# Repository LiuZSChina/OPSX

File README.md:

# OPSX Sonnar
An open sourced Polaroid SX-70 core board with sonnar support.Based on the [OPSX project](https://github.com/sunyitong/OPSX).\
开源的宝丽来sx-70核心板，可以支持带有声呐对焦的设备。基于[OPSX 项目](https://github.com/sunyitong/OPSX)开发。

This is an open sourced Polaroid SX-70 instant camera core board with the Raspberry Pi RP2040 as the MCU. The aim of this project is to provide a fully resource accessible and hobbyist friendly replacement core board. It offers more extensibility and hacking ideas while implementing all the features of the original camera.\
本项目是开源的宝丽来sx-70核心板，该项目使用树莓派rp2040构建而成，本项目的目的是为爱好者提供一个可以完全自主掌控的核心板，在保留原机器各种功能的同时可以发挥自己的创意进行功能拓展。

The structure of the repository:\
本项目仓库的结构：

1. The [Original](https://github.com/LiuZSChina/OPSX/tree/master/Original) file contains design for non-sonnar sx-70.See README.md inside this folder for details.\
[Original](https://github.com/LiuZSChina/OPSX/tree/master/Original)文件夹内是适合没有声呐对焦sx70的核心板设计，设计来自于原本的[OPSX 项目](https://github.com/sunyitong/OPSX)，文件夹内具体项目的作用详见文件夹内的README.md

2. The [Sonar](https://github.com/LiuZSChina/OPSX/tree/master/Sonnar) file contains design for sonnar sx-70.See README.md inside this folder for details.\
[Original](https://github.com/LiuZSChina/OPSX/tree/master/Original)文件夹内是新设计的适用于声呐对焦的sx70核心板及附件，文件夹内具体项目的作用详见文件夹内的README.md。

## Table of Contents

- [OPSX](#opsx)
  - [Hardware](#hardware)
    - [Fabrication](#fabrication)
  - [Software](#software)
    - [Uploading](#uploading)
  - [Contributor](#contributor)
  - [License](#license)

## Hardware
> Remander: You are going to need some “basic” tools:   soldering iron with a fine tip, a prying tool and a tweezer.\
Aside from the usual tools you are going to need what is called a “Polaroid screwdriver” or “SX-70 screwdriver”, since most of the cameras use a special “square 1mm x 1mm” screws. You could either buy one or fabricate one yourself.\
please read the [Disassembly Guide](https://instantphotography.files.wordpress.com/2010/12/polaroid-sx-70-camera-repair-book.pdf) or [SX70 camera 125ASA to 600ASA conversion](https://opensx70.com/tutorials/100-600-conversion/) first.\
提示：首先你需要一些基本的工具：电烙铁、撬棒和镊子。\
其次大多数sx70相机的螺丝都是非常特殊的1mm x 1mm 宝丽来螺丝，所以你需要使用特殊的螺丝刀才能拆卸，买一把或者自己磨一个都可以。\
在操作之前推荐先浏览[Disassembly Guide](https://instantphotography.files.wordpress.com/2010/12/polaroid-sx-70-camera-repair-book.pdf) 或者 [SX70 camera 125ASA to 600ASA conversion](https://opensx70.com/tutorials/100-600-conversion/).

### Fabrication
Please select a **dual copper layer PCB** with a thickness of **0.8 mm** or less for fabrication.\
制造时请选择 FR-4基板，双层板，厚度0.8mm或者更小（会贵）。

## Software
TODO

### Uploading
Solder U+ U- GND VCC to a standard usb cable to connect to your computer. Then you can treat it as normal raspberry pico device. See [here](https://www.raspberrypi.com/documentation/microcontrollers/rp2040.html#raspberry-pi-pico) for more information about uploading.\
把板子上的U+ U- GND VCC焊到usb线上，连接电脑后可以当作树莓派Pico开发板进行操作，具体上传的方法在[这里](https://www.raspberrypi.com/documentation/microcontrollers/rp2040.html#raspberry-pi-pico)。

## Contributor
[@Yitong Sun](https://github.com/sunyitong) - a PhD candidate in the Computer Science Research Centre at the Royal College of Art.[RCA website](https://www.rca.ac.uk/research-innovation/research-degrees/research-students/yitong-sun/) - [E-mail](yitong.sun@network.rca.ac.uk)

[@LiuZS](https://github.com/LiuZSChina) - ？
## License
Any distribution or modification based on this project should be clearly attributed to the source.
[GPL 3.0](LICENSE)

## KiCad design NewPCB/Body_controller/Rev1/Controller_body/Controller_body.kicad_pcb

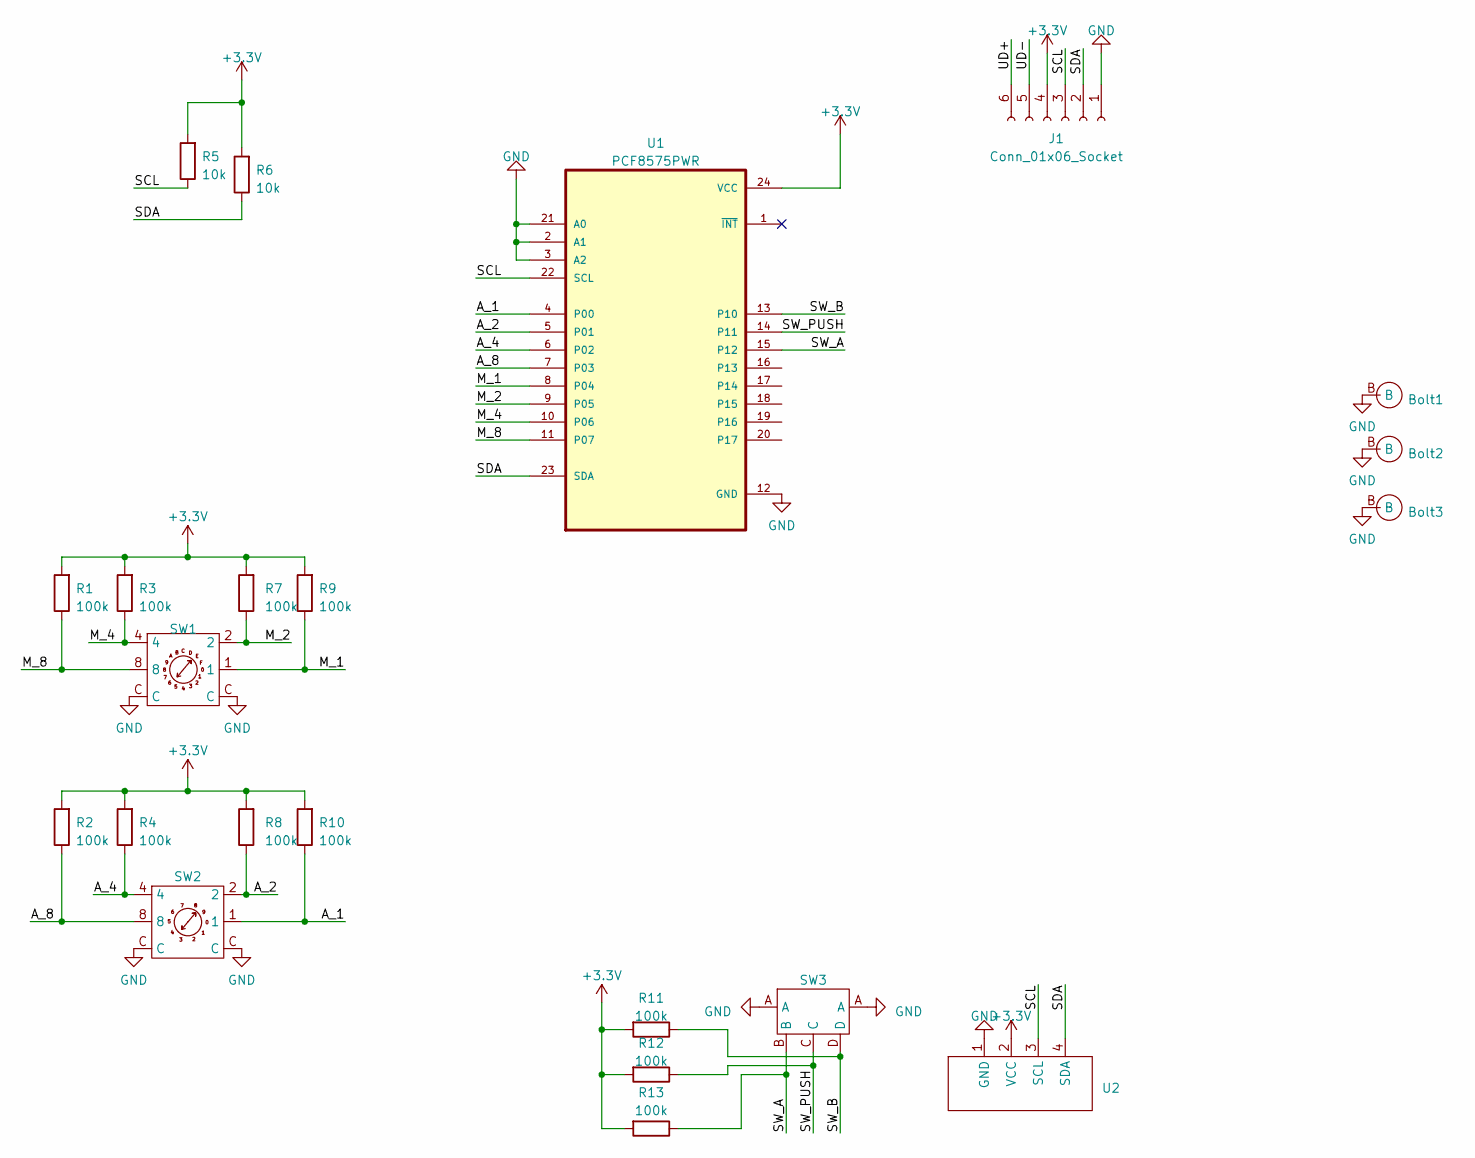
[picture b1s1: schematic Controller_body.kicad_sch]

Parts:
Bolt1, Bolt2, Bolt3: M3_Bolt
J1: Conn_01x06_Socket; TE_84953-6_1x06-1MP_P1.0mm_Horizontal
R1, R2, R3, R4, R7, R8, R9, R10, R11, R12, R13: 100k; R_0805_2012Metric_Pad1.20x1.40mm_HandSolder
R5, R6: 10k; R_0805_2012Metric_Pad1.20x1.40mm_HandSolder
SW1: GSMR_16
SW2: GSMR_10S
SW3: Direction3 Pin5
U1: PCF8575PWR; SOP65P640X120-24N
U2: OLED 0.96 i2c

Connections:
+3.3V: J1.4, R1.2, R2.2, R3.2, R4.2, R5.2, R6.2, R7.2, R8.2, R9.2, R10.2, R11.2, R12.2, R13.2, U1.24 (VCC), U2.2 (VCC)
/A_1: R10.1, SW2.1, U1.4 (P00)
/A_2: R8.1, SW2.2, U1.5 (P01)
/A_4: R4.1, SW2.4, U1.6 (P02)
/A_8: R2.1, SW2.8, U1.7 (P03)
/M_1: R9.1, SW1.1, U1.8 (P04)
/M_2: R7.1, SW1.2, U1.9 (P05)
/M_4: R3.1, SW1.4, U1.10 (P06)
/M_8: R1.1, SW1.8, U1.11 (P07)
/SCL: J1.3, R5.1, U1.22 (SCL), U2.3 (SCL)
/SDA: J1.2, R6.1, U1.23 (SDA), U2.4 (SDA)
/SW_A: R13.1, SW3.B, U1.15 (P12)
/SW_B: R11.1, SW3.D, U1.13 (P10)
/SW_PUSH: R12.1, SW3.C, U1.14 (P11)
/UD+: J1.6
/UD-: J1.5
GND: Bolt1.B, Bolt2.B, Bolt3.B, J1.1, SW1.C, SW2.C, SW3.A, U1.2 (A1), U1.3 (A2), U1.12 (GND), U1.21 (A0), U2.1 (GND)

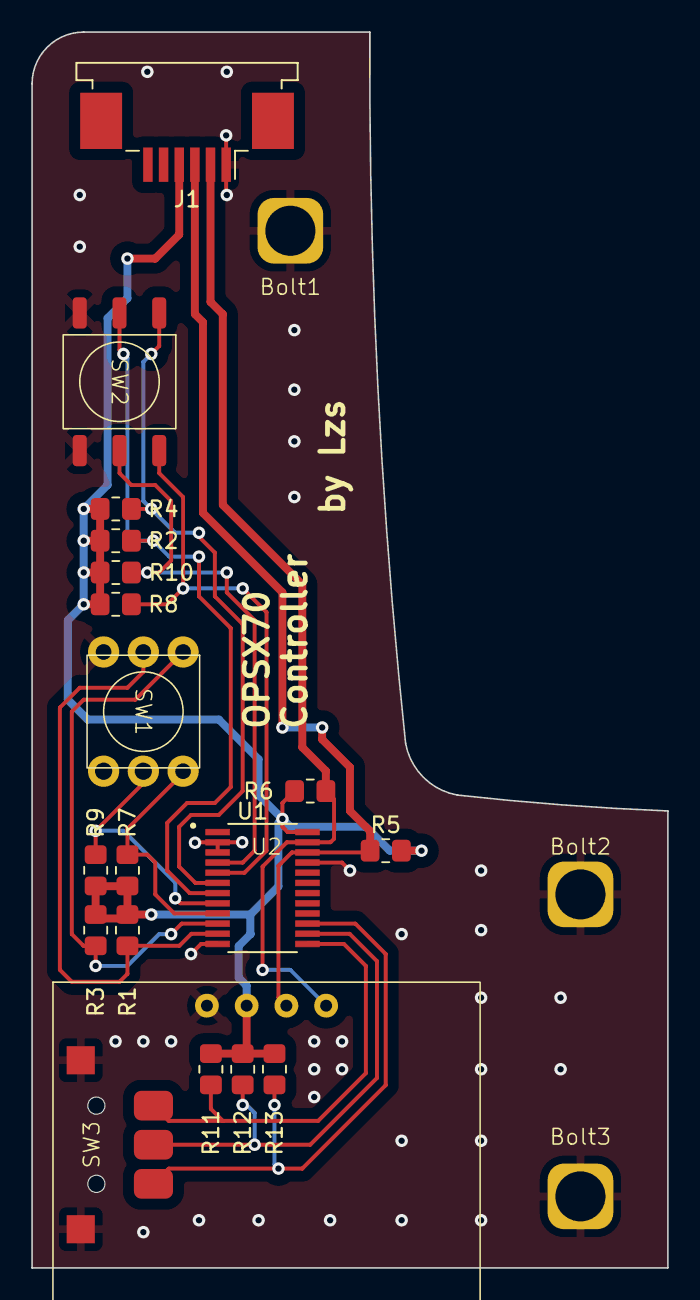
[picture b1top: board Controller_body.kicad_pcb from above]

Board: 2 copper layers, 40.6 x 79.0 mm, 22 parts (0 on the bottom side), 15 nets.

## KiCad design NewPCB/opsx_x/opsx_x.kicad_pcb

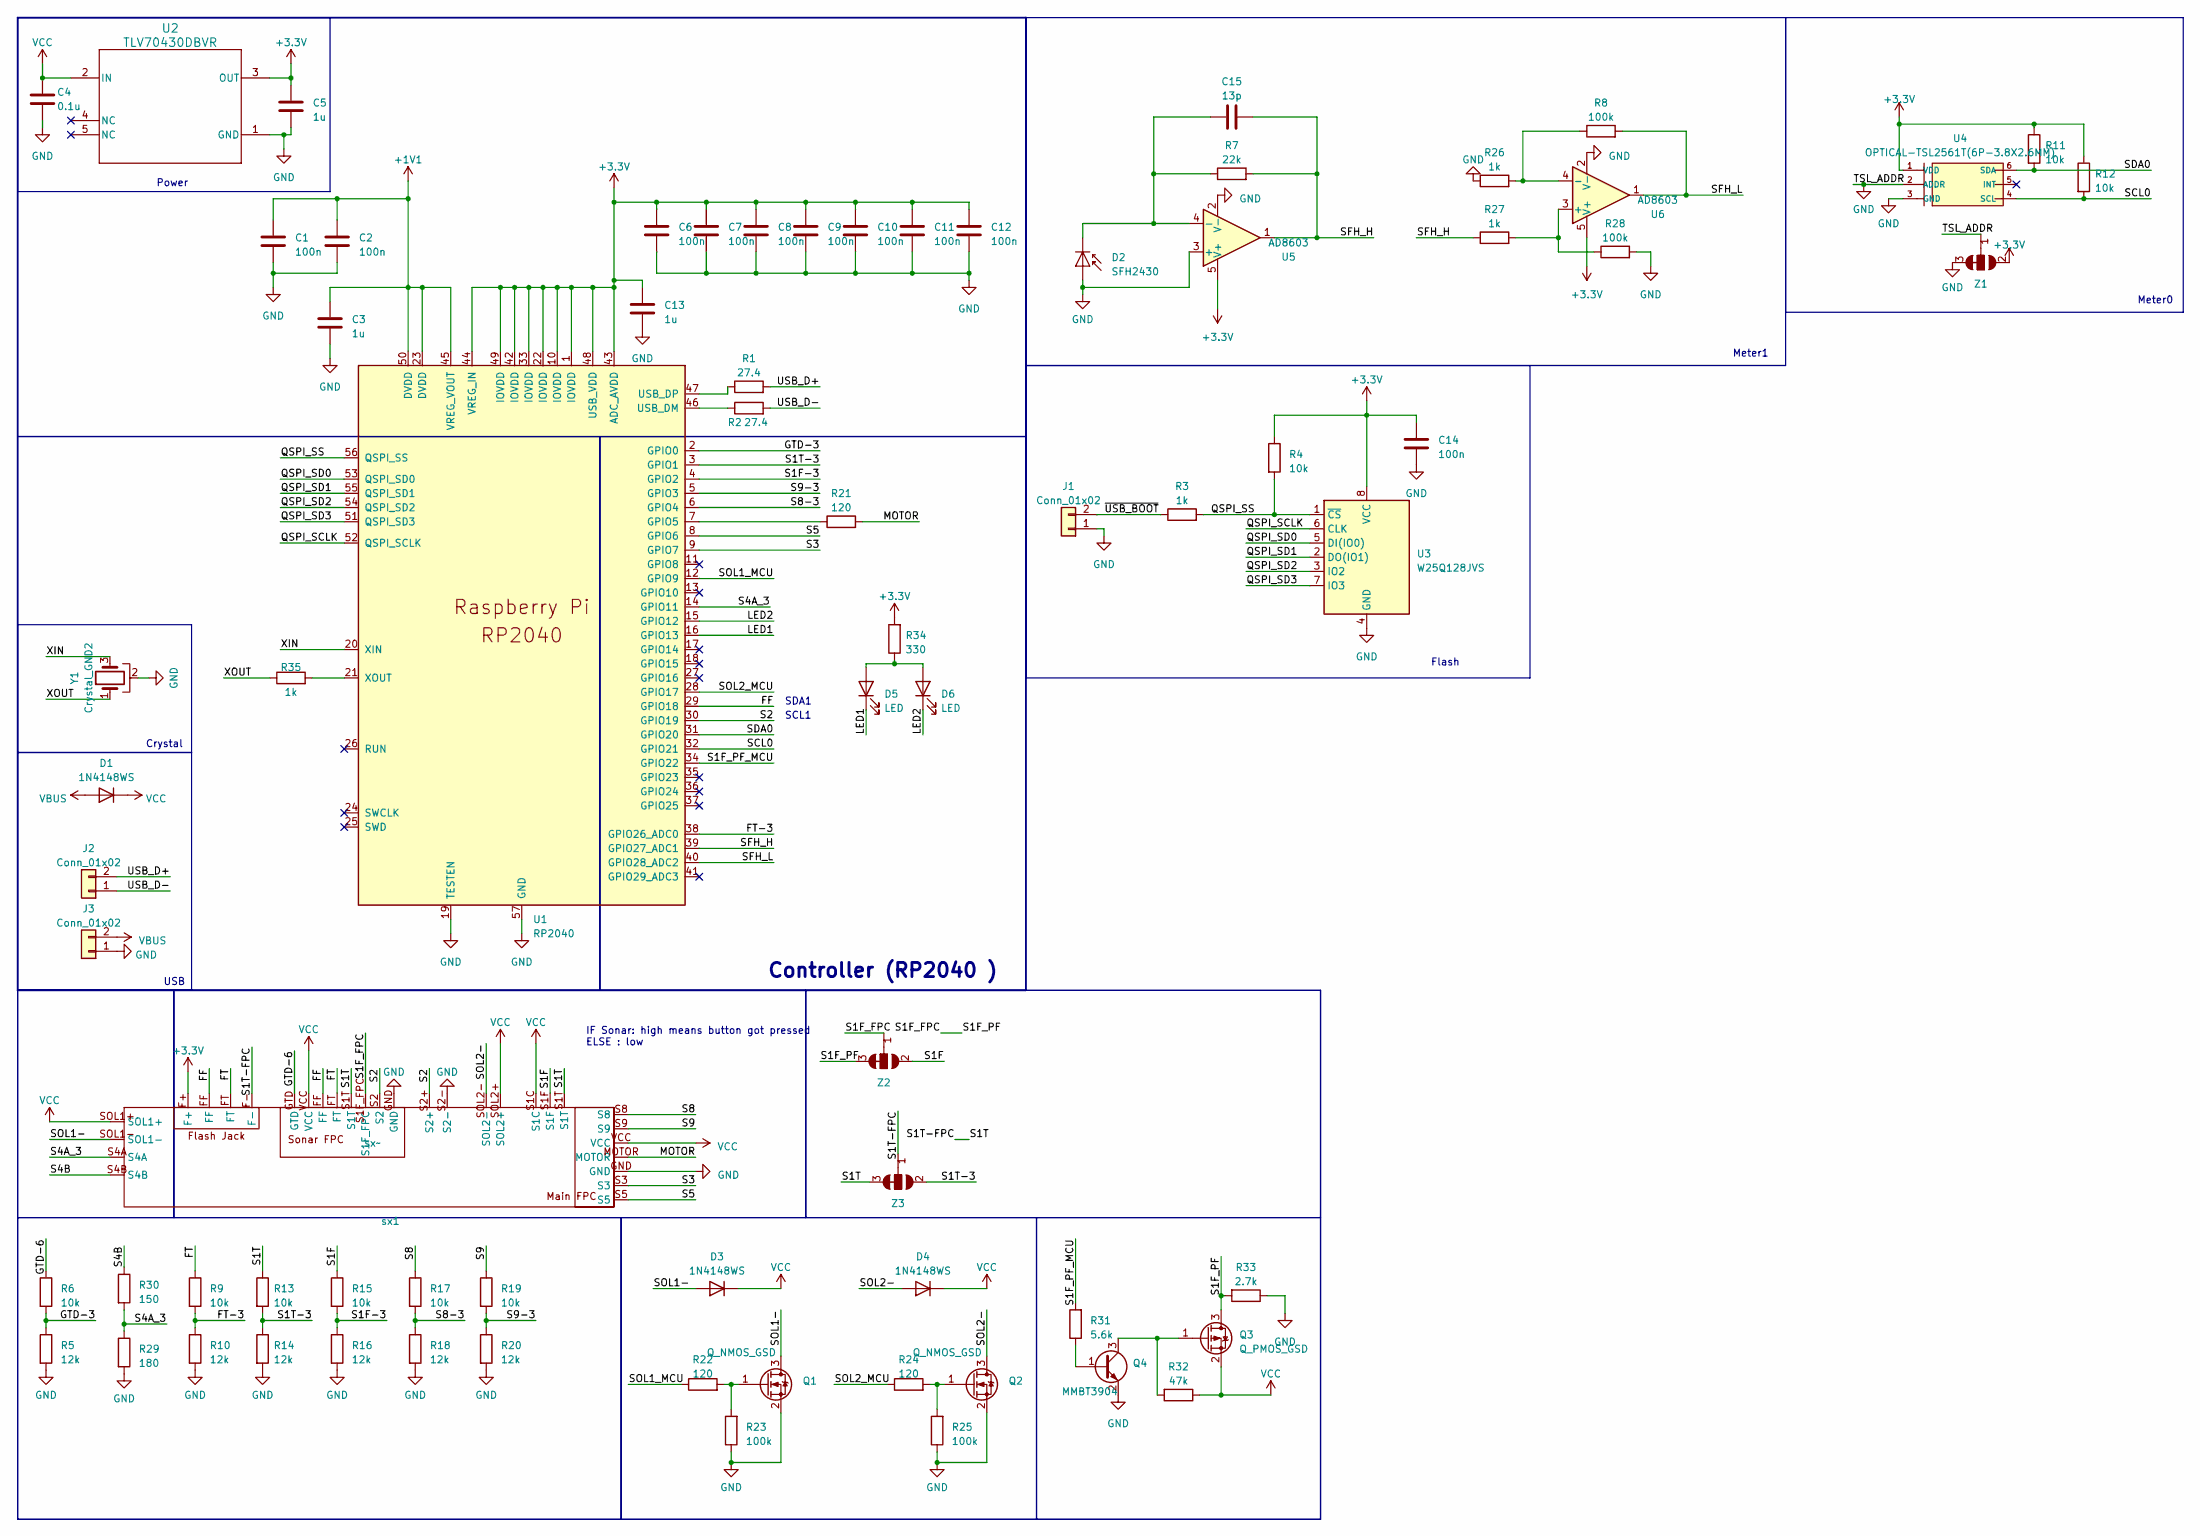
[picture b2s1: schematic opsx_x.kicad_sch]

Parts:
C1, C2, C6, C7, C8, C9, C10, C11, C12, C14: 100n; C_0402_1005Metric_Pad0.74x0.62mm_HandSolder
C3, C5, C13: 1u; C_0402_1005Metric_Pad0.74x0.62mm_HandSolder
C4: 0.1u; C_0402_1005Metric_Pad0.74x0.62mm_HandSolder
C15: 13p; C_0402_1005Metric_Pad0.74x0.62mm_HandSolder
D1, D3, D4: 1N4148WS; D_SOD-323
D2: SFH2430; Osram_SFH2430
D5, D6: LED; D_0603_1608Metric_Pad1.05x0.95mm_HandSolder
J1, J2, J3: Conn_01x02; PinHeader_1x02_P2.54mm_Vertical
Q1, Q2: Q_NMOS_GSD; SOT-23
Q3: Q_PMOS_GSD; SOT-23
Q4: MMBT3904; SOT-23
R1, R2: 27.4; R_0402_1005Metric_Pad0.72x0.64mm_HandSolder
R3, R26, R27, R35: 1k; R_0402_1005Metric_Pad0.72x0.64mm_HandSolder
R4, R6, R9, R11, R12, R13, R15, R17, R19: 10k; R_0402_1005Metric_Pad0.72x0.64mm_HandSolder
R5, R10, R14, R16, R18, R20: 12k; R_0402_1005Metric_Pad0.72x0.64mm_HandSolder
R7: 22k; R_0805_2012Metric_Pad1.20x1.40mm_HandSolder
R8, R23, R25, R28: 100k; R_0402_1005Metric_Pad0.72x0.64mm_HandSolder
R21, R22, R24: 120; R_0402_1005Metric_Pad0.72x0.64mm_HandSolder
R29: 180; R_0402_1005Metric_Pad0.72x0.64mm_HandSolder
R30: 150; R_0402_1005Metric_Pad0.72x0.64mm_HandSolder
R31: 5.6k; R_0402_1005Metric_Pad0.72x0.64mm_HandSolder
R32: 47k; R_0402_1005Metric_Pad0.72x0.64mm_HandSolder
R33: 2.7k; R_0402_1005Metric_Pad0.72x0.64mm_HandSolder
R34: 330; R_0402_1005Metric_Pad0.72x0.64mm_HandSolder
U1: RP2040; RP2040-QFN-56
U2: TLV70430DBVR; DBV0005A_N
U3: W25Q128JVS; SOIC-8_5.23x5.23mm_P1.27mm
U4: OPTICAL-TSL2561T(6P-3.8X2.6MM); TMB6-1.55-3.8X2.6MM; MPN TSL2561T
U5, U6: AD8603; TSOT-23-5
Y1: Crystal_GND2; Resonator_SMD_Murata_CSTxExxV-3Pin_3.0x1.1mm
Z1, Z2, Z3: Selector_default
sx1: sx~; sx70

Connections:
+1V1: C1.1, C2.1, C3.1, U1.23 (DVDD), U1.45 (VREG_VOUT), U1.50 (DVDD)
+3.3V: C5.1, C6.1, C7.1, C8.1, C9.1, C10.1, C11.1, C12.1, C13.1, C14.1, R4.1, R11.1, R12.1, R34.2, U1.1 (IOVDD), U1.10 (IOVDD), U1.22 (IOVDD), U1.33 (IOVDD), U1.42 (IOVDD), U1.43 (ADC_AVDD), U1.44 (VREG_IN), U1.48 (USB_VDD), U1.49 (IOVDD), U2.3 (OUT), U3.8 (VCC), U4.1 (VDD), U5.5 (V+), U6.5 (V+), Z1.1, sx1.F+
/FF: U1.29 (GPIO18), sx1.FF
/FT: R9.1, sx1.FT
/FT-3: R9.2, R10.1, U1.38 (GPIO26_ADC0)
/GTD-3: R5.1, R6.2, U1.2 (GPIO0)
/GTD-6: R6.1, sx1.GTD
/LED1: D5.1 (K), U1.16 (GPIO13)
/LED2: D6.1 (K), U1.15 (GPIO12)
/MOTOR: R21.2, sx1.MOTOR
/QSPI_SCLK: U1.52 (QSPI_SCLK), U3.6 (CLK)
/QSPI_SD0: U1.53 (QSPI_SD0), U3.5 (DI(IO0))
/QSPI_SD1: U1.55 (QSPI_SD1), U3.2 (DO(IO1))
/QSPI_SD2: U1.54 (QSPI_SD2), U3.3 (IO2)
/QSPI_SD3: U1.51 (QSPI_SD3), U3.7 (IO3)
/QSPI_SS: R3.2, R4.2, U1.56 (QSPI_SS), U3.1 (~CS)
/S1F: R15.1, Z2.1, sx1.S1F
/S1F-3: R15.2, R16.1, U1.4 (GPIO2)
/S1F_FPC: Q3.3 (D), R33.2, Z2.2, Z2.3, sx1.S1F_FPC
/S1F_PF_MCU: R31.2, U1.34 (GPIO22)
/S1T: R13.1, Z3.2, Z3.3, sx1.F-, sx1.S1T
/S1T-3: R13.2, R14.1, U1.3 (GPIO1), Z3.1
/S2: U1.30 (GPIO19), sx1.S2, sx1.S2+
/S3: U1.9 (GPIO7), sx1.S3
/S4A_3: R29.1, R30.2, U1.14 (GPIO11), sx1.S4A
/S4B: R30.1, sx1.S4B
/S5: U1.8 (GPIO6), sx1.S5
/S8: R17.1, sx1.S8
/S8-3: R17.2, R18.1, U1.6 (GPIO4)
/S9: R19.1, sx1.S9
/S9-3: R19.2, R20.1, U1.5 (GPIO3)
/SCL0: R12.2, U1.32 (GPIO21), U4.4 (SCL)
/SDA0: R11.2, U1.31 (GPIO20), U4.6 (SDA)
/SFH_H: C15.2, R7.2, R27.1, U1.39 (GPIO27_ADC1), U5.1
/SFH_L: R8.2, U1.40 (GPIO28_ADC2), U6.1
/SOL1-: D3.2 (A), Q1.3 (D), sx1.SOL1-
/SOL1_MCU: R22.1, U1.12 (GPIO9)
/SOL2-: D4.2 (A), Q2.3 (D), sx1.SOL2-
/SOL2_MCU: R24.1, U1.28 (GPIO17)
/USB_D+: J2.2, R1.2
/USB_D-: J2.1, R2.2
/XIN: U1.20 (XIN), Y1.3
/XOUT: R35.1, Y1.1
/~USB_BOOT: J1.2, R3.1
GND: C1.2, C2.2, C3.2, C4.2, C5.2, C6.2, C7.2, C8.2, C9.2, C10.2, C11.2, C12.2, C13.2, C14.2, D2.2 (A), J1.1, J3.1, Q1.2 (S), Q2.2 (S), Q4.2 (E), R5.2, R10.2, R14.2, R16.2, R18.2, R20.2, R23.1, R25.1, R26.1, R28.2, R29.2, R33.1, U1.19 (TESTEN), U1.57 (GND), U2.1 (GND), U3.4 (GND), U4.2 (ADDR), U4.3 (GND), U5.2 (V-), U5.3 (+), U6.2 (V-), Y1.2, Z1.2, Z1.3, sx1.GND, sx1.S2-
unnamed: C15.1, D2.1 (K), R7.1, U5.4 (-)
unnamed: D5.2 (A), D6.2 (A), R34.1
unnamed: Q1.1 (G), R22.2, R23.2
unnamed: Q2.1 (G), R24.2, R25.2
unnamed: Q3.1 (G), Q4.3 (C), R32.2
unnamed: Q4.1 (B), R31.1
unnamed: R21.1, U1.7 (GPIO5)
unnamed: R2.1, U1.46 (USB_DM)
unnamed: R1.1, U1.47 (USB_DP)
unnamed: R35.2, U1.21 (XOUT)
unnamed: R27.2, R28.1, U6.3 (+)
unnamed: R8.1, R26.2, U6.4 (-)
VBUS: D1.2 (A), J3.2
VCC: C4.1, D1.1 (K), D3.1 (K), D4.1 (K), Q3.2 (S), R32.1, U2.2 (IN), sx1.S1C, sx1.SOL1+, sx1.SOL2+, sx1.VCC

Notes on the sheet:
Flash
Meter0
Power
Crystal
IF Sonar: high means button got pressed ELSE : low
Controller (RP2040 )
Meter1
SCL1
SDA1
USB

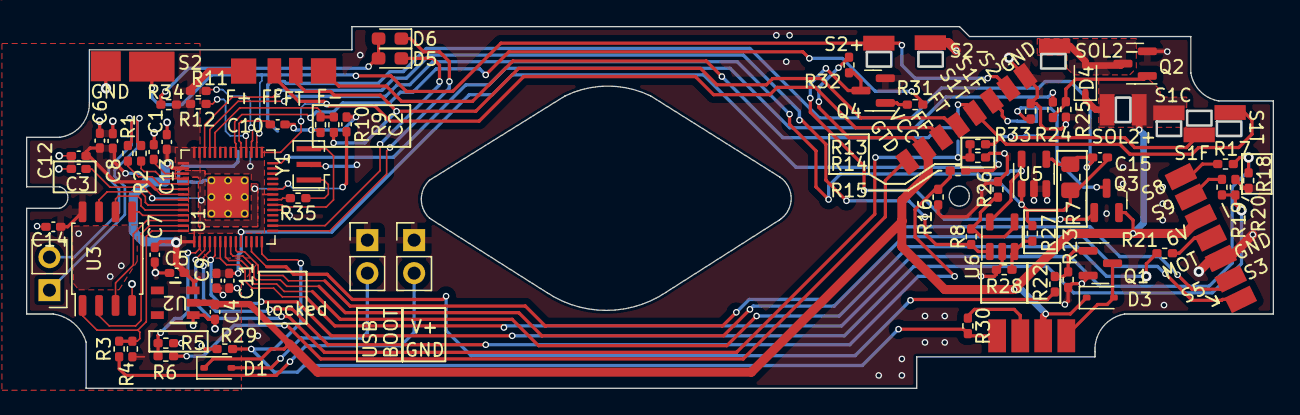
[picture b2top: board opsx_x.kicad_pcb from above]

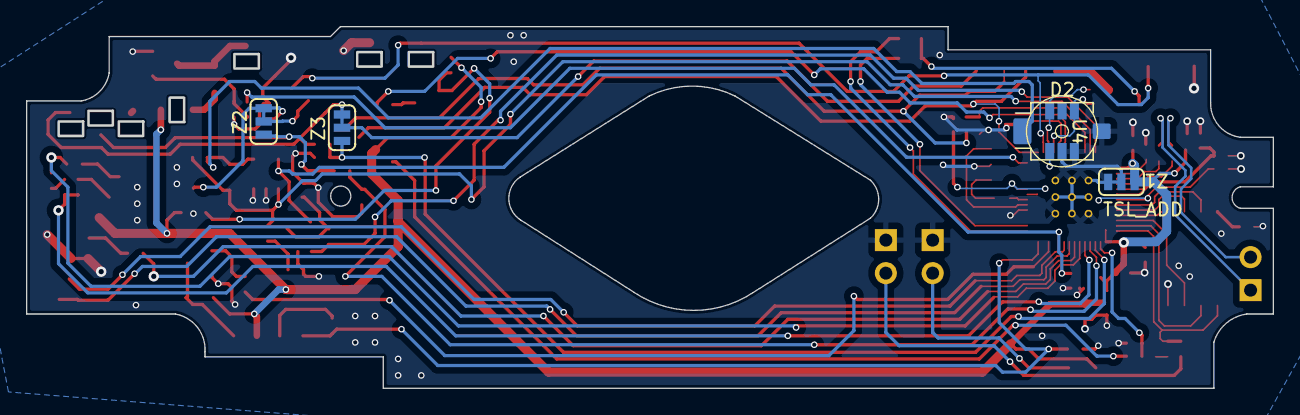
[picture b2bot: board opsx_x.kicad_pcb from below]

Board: 2 copper layers, 95.8 x 27.7 mm, 74 parts (5 on the bottom side), 59 nets.

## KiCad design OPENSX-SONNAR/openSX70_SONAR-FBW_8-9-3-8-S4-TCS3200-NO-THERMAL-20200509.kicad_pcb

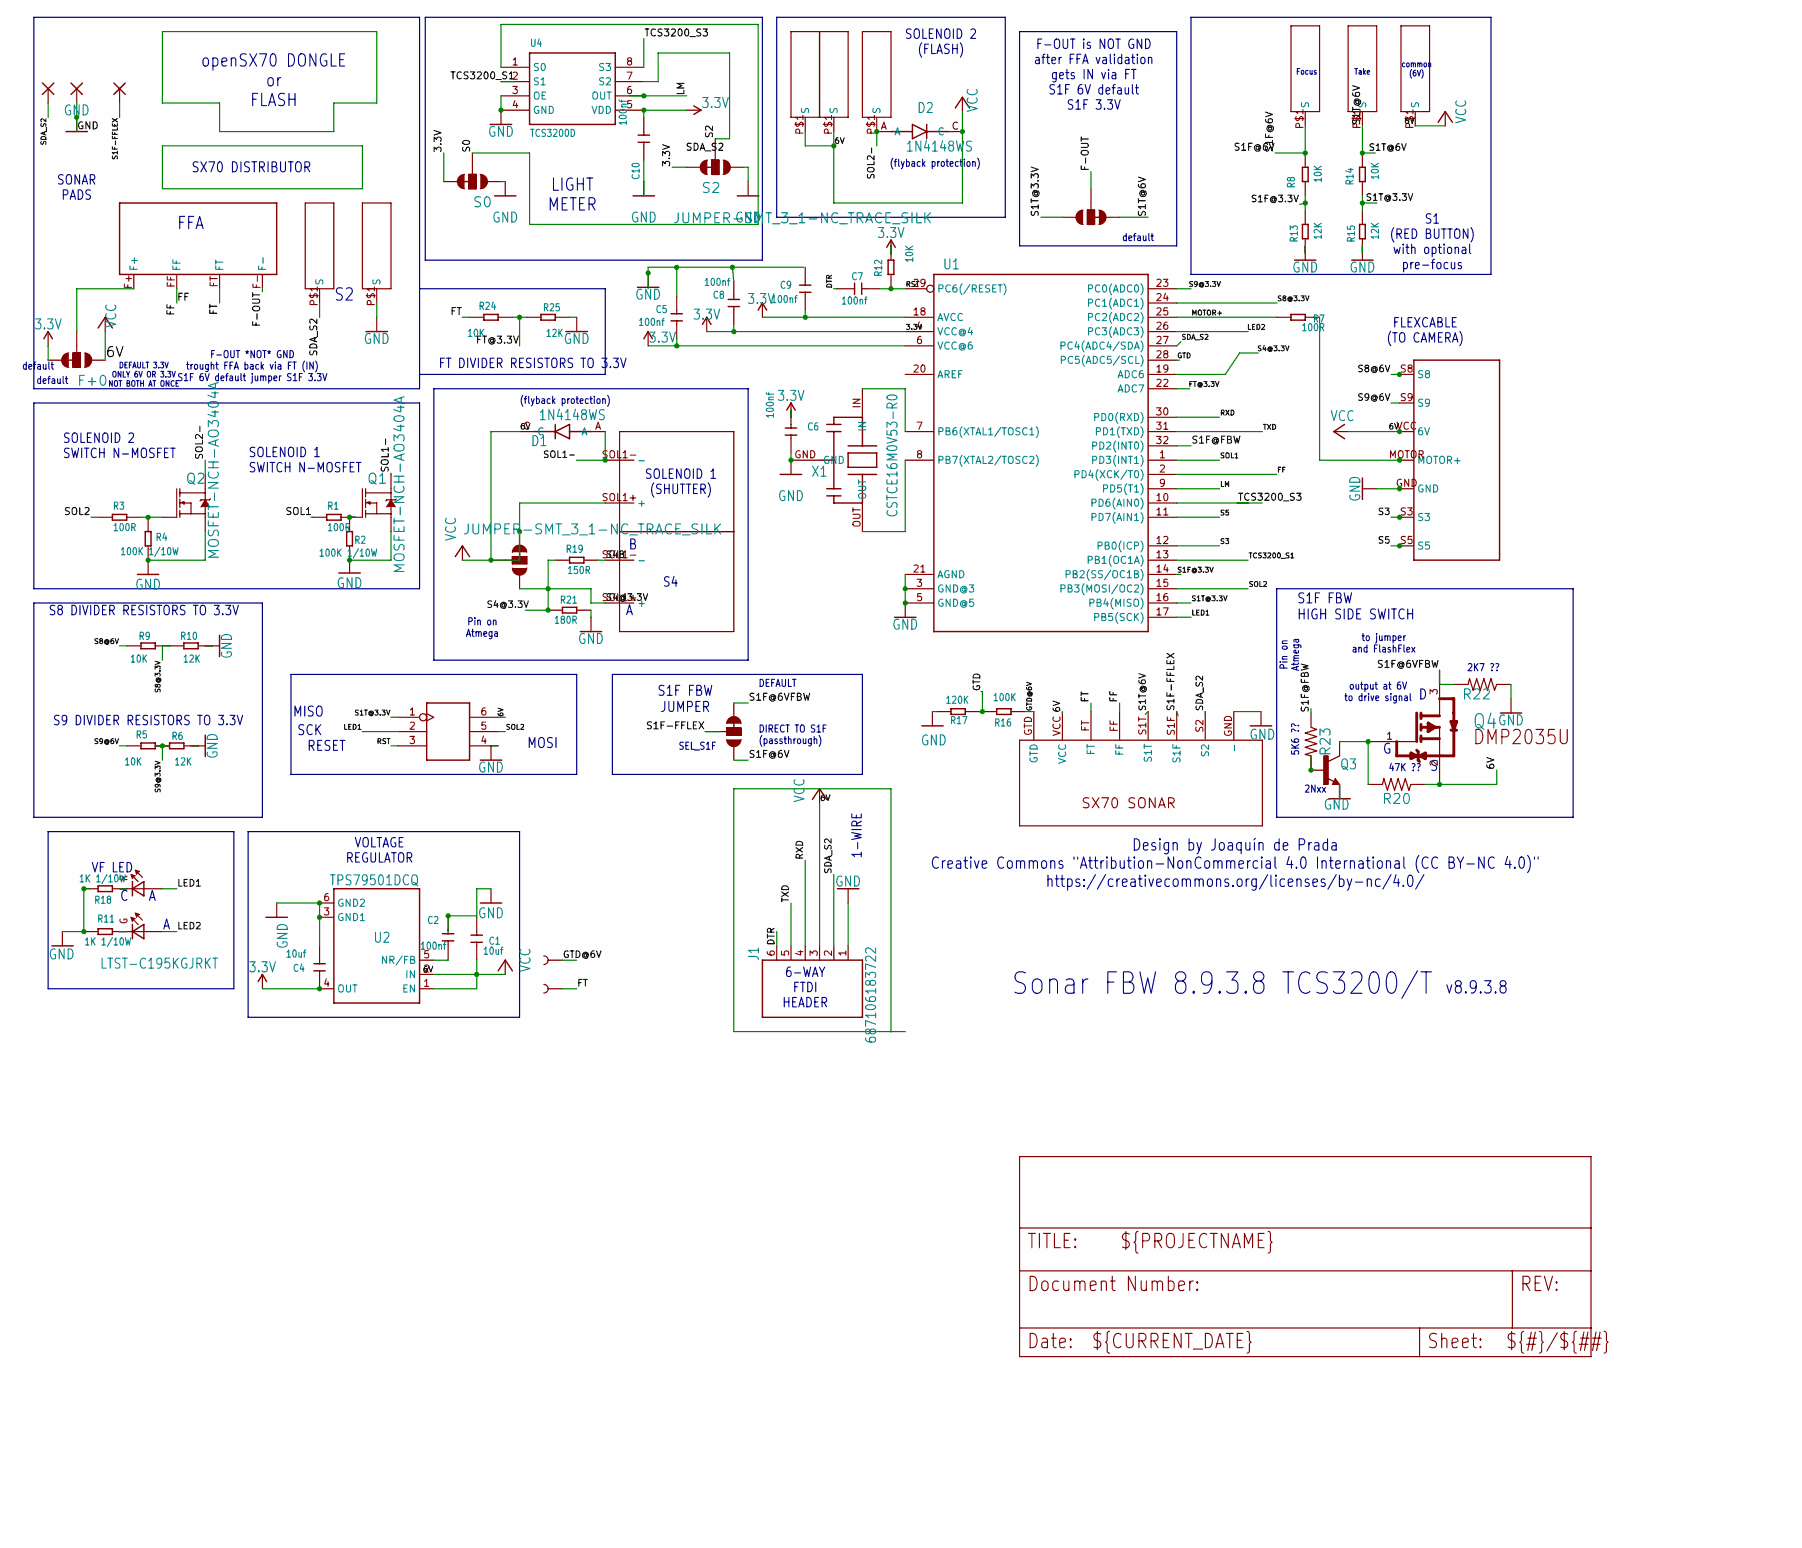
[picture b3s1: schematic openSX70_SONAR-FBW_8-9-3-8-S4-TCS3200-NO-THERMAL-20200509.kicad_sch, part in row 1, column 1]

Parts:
C1, C4: 10uf; C0603
C2, C5, C6, C7, C8, C9, C10: 100nf; C0603
D1, D2: 1N4148WS; SODFL2512X100N
F+0: JUMPER-SMT_3_1-NC_TRACE_SILK; SMT-JUMPER_3_1-NC_TRACE_SILK
ICSP0: ICSP; H2X3-2.54
J1: 687106183722
LED0: LTST-C195KGJRKT; LTST-BILED-15X16
Q1, Q2: MOSFET-NCH-AO3404A; SOT23-3
Q3: -NPN-SOT23-BEC; SOT23-BEC
Q4: DIODES_INC._DMP2035UDIODES_INC._DMP2035U_0_2; DIODES_INC._DMP2035U_2
R1, R3, R7: 100R; R0603
R2, R4: 100K 1/10W; R0603
R5, R8, R9, R12, R14, R24: 10K; R0603
R6, R10, R13, R15, R25: 12K; R0603
R11, R18: 1K 1/10W; R0603
R16: 100K; R0603
R17: 120K; R0603
R19: 150R; R0603
R20, R22, R23: RESISTOR0603; 0603
R21: 180R; R0603
S0, S2: JUMPER-SMT_3_1-NC_TRACE_SILK; SMT-JUMPER_3_1-NC_TRACE_SILK
S1-0, S1F+0, S1T+0, S2+0, S2-0: SX70-S-PAD-NEW; SX70-S-PAD2
S4: SX70-SOLENOID1-2PADS; SX70-SOLENOID1-2
SEL_F-0: JUMPER-SMT_3_1-NC_TRACE_SILK; SMT-JUMPER_3_1-NC_TRACE_SILK
SEL_S1F0, SEL_S4: JUMPER-SMT_3_1-NC_TRACE_SILK; SMT-JUMPER_3_1-NC_TRACE_SILK
SOL1: SX70-SOLENOID1-2PADS; SX70-SOLENOID1-2
SOL2+0, SOL2+1, SOL2-0: SX70-S-PAD-NEW; SX70-S-PAD2
TP1, TP4: TEST-POINT3X4; PAD.03X.04
U1: ATMEGA328P_32MLFATMEGA328-MLF; MLF32
U2: TPS79501DCQ; SOT127P706X180-6N
U4: TCS3200D; SOIC8
U$1: SX70-7-PAD; SX70-7-PAD-PROPER
U$2: FFA; FFA-PAD-PACKAGE
U$3: SX70-SONAR-FLASHFLEX; SONAR-FLASHFLEX
U$5, U$6: S2-SONAR
U$7: GND-SONAR
X1: CSTCE16M0V53-R0; CFP95P160X100-3N

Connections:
3.3V: C4.2, C5.1, C6.1, C8.1, C9.1, C10.1, F+0.3, R12.2, S0.3, S2.3, U1.4 (VCC@4), U1.6 (VCC@6), U1.18 (AVCC), U2.4 (OUT), U4.5 (VDD)
6V: C1.2, D1.C, D2.C, F+0.1, ICSP0.6 (VCC), J1.3 (4), Q4.2 (S), R20.1, S1-0.P$1, SEL_S4.2, SEL_S4.3, SOL1.SOL1+ (+), SOL2+0.P$1, SOL2+1.P$1, U2.1 (EN), U2.2 (IN), U$1.VCC (6V), U$3.VCC
DTR: C7.1, J1.6 (1)
F-OUT: SEL_F-0.2, U$2.F-
FF: U1.2 (PD4(XCK/T0)), U$2.FF, U$3.FF
FT: R24.1, TP4.P$1, U$2.FT, U$3.FT
FT@3.3V: R24.2, R25.1, U1.22 (ADC7)
GND: C1.1, C2.1, C4.1, C5.2, C6.2, C8.2, C10.2, ICSP0.4 (GND), J1.1 (6), Q1.2 (S), Q2.2 (S), Q3.E, R2.1, R4.1, R6.2, R10.2, R11.1, R13.1, R15.1, R17.1, R18.2, R21.1, R22.1, R25.2, S0.1, S2.1, S2-0.P$1, U1.3 (GND@3), U1.5 (GND@5), U1.21 (AGND), U2.3 (GND1), U2.6 (GND2), U4.3 (OE), U4.4 (GND), U$1.GND, U$3.GND (-), U$7.GND-SONAR, X1.GND
GTD: R16.2, R17.2, U1.28 (PC5(ADC5/SCL))
GTD@6V: R16.1, TP1.P$1, U$3.GTD
LED1: ICSP0.2 (SCK), LED0.P$2 (A2), U1.17 (PB5(SCK))
LED2: LED0.P$1 (A1), U1.26 (PC3(ADC3))
LM: U1.9 (PD5(T1)), U4.6 (OUT)
MOTOR+: R7.1, U1.25 (PC2(ADC2))
MOTOR-HEADER: R7.2, U$1.MOTOR (MOTOR+)
unnamed: Q1.1 (G), R1.2, R2.2
unnamed: LED0.P$4 (K2), R18.1
unnamed: Q2.1 (G), R3.2, R4.2
unnamed: U1.7 (PB6(XTAL1/TOSC1)), X1.IN
unnamed: F+0.2, U$2.F+
unnamed: U1.8 (PB7(XTAL2/TOSC2)), X1.OUT
unnamed: Q3.C, Q4.1 (G), R20.2
unnamed: Q3.B, R23.2
unnamed: C2.2, U2.5 (NR/FB)
unnamed: LED0.P$3 (K1), R11.2
RST: C7.2, ICSP0.3 (RST), R12.1, U1.29 (PC6(/RESET))
RXD: J1.4 (3), U1.30 (PD0(RXD))
S0: S0.2, U4.1 (S0)
S1F-FFLEX: SEL_S1F0.2, U$3.S1F, U$6.S2-SONAR
S1F@3.3V: R8.1, R13.2, U1.14 (PB2(SS/OC1B))
S1F@6V: R8.2, S1F+0.P$1, SEL_S1F0.1
S1F@6VFBW: Q4.3 (D), R22.2, SEL_S1F0.3
S1F@FBW: R23.1, U1.32 (PD2(INT0))
S1T@3.3V: ICSP0.1 (MISO), R14.1, R15.2, SEL_F-0.1, U1.16 (PB4(MISO))
S1T@6V: R14.2, S1T+0.P$1, SEL_F-0.3, U$3.S1T
S2: S2.2, U4.7 (S2)
S3: U1.12 (PB0(ICP)), U$1.S3
S4@3.3V: R19.1, R21.2, S4.SOL1+ (+), SEL_S4.1, U1.19 (ADC6)
S4B: R19.2, S4.SOL1- (-)
S5: U1.11 (PD7(AIN1)), U$1.S5
S8@3.3V: R9.2, R10.1, U1.24 (PC1(ADC1))
S8@6V: R9.1, U$1.S8
S9@3.3V: R5.2, R6.1, U1.23 (PC0(ADC0))
S9@6V: R5.1, U$1.S9
SDA_S2: J1.2 (5), S2+0.P$1, U1.27 (PC4(ADC4/SDA)), U$3.S2, U$5.S2-SONAR
SOL1: R1.1, U1.1 (PD3(INT1))
SOL1-: D1.A, Q1.3 (D), SOL1.SOL1- (-)
SOL2: ICSP0.5 (MOSI), R3.1, U1.15 (PB3(MOSI/OC2))
SOL2-: D2.A, Q2.3 (D), SOL2-0.P$1
TCS3200_S1: U1.13 (PB1(OC1A)), U4.2 (S1)
TCS3200_S3: U1.10 (PD6(AIN0)), U4.8 (S3)
TXD: J1.5 (2), U1.31 (PD1(TXD))

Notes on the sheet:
FLEXCABLE (TO CAMERA)
(flyback protection)
S1 (RED BUTTON) with optional pre-focus
SOLENOID 1 SWITCH N-MOSFET
default
v8.9.3.8
SCK
DEFAULT
Pin on Atmega
1-WIRE
openSX70 DONGLE or FLASH
output at 6V to drive signal
S9 DIVIDER RESISTORS TO 3.3V
VF LED
FT DIVIDER RESISTORS TO 3.3V
S8 DIVIDER RESISTORS TO 3.3V
2Nxx
47K ??
SOLENOID 1 (SHUTTER)
F-OUT is NOT GND after FFA validation gets IN via FT S1F 6V default S1F 3.3V
F-OUT *NOT* GND trought FFA back via FT (IN) S1F 6V default jumper S1F 3.3V
Focus
5K6 ??
LIGHT METER
Take
DIRECT TO S1F (passthrough)
MISO
SEL_S1F
SX70 DISTRIBUTOR
SOLENOID 2 SWITCH N-MOSFET
RESET
S1F FBW JUMPER
6-WAY FTDI HEADER
common (6V)
MOSI
VOLTAGE REGULATOR
2K7 ??
SONAR PADS
Sonar FBW 8.9.3.8 TCS3200/T
Design by Joaquín de Prada Creative Commons "Attribution-NonCommercial 4.0 International (CC BY-NC 4.0)" https://creativecommons.org/licenses/by-nc/4.0/

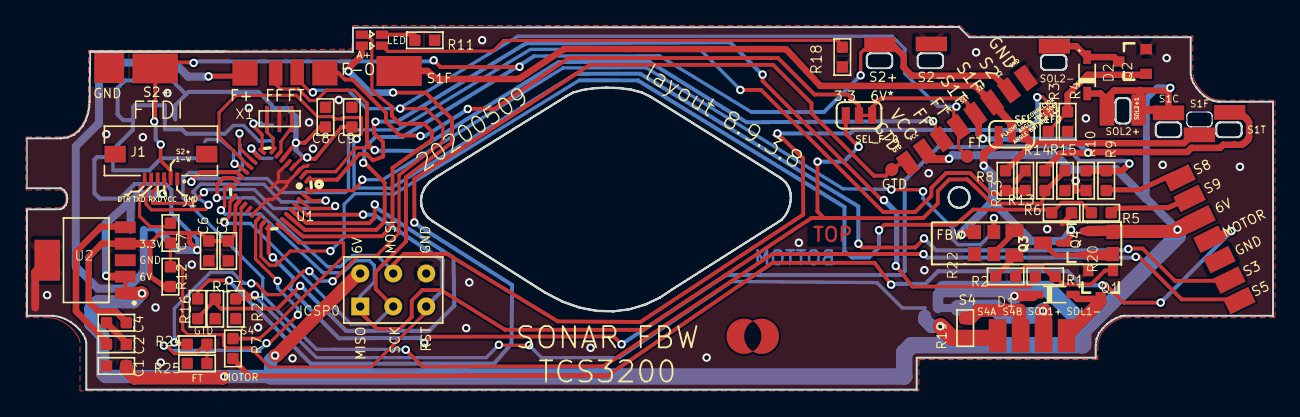
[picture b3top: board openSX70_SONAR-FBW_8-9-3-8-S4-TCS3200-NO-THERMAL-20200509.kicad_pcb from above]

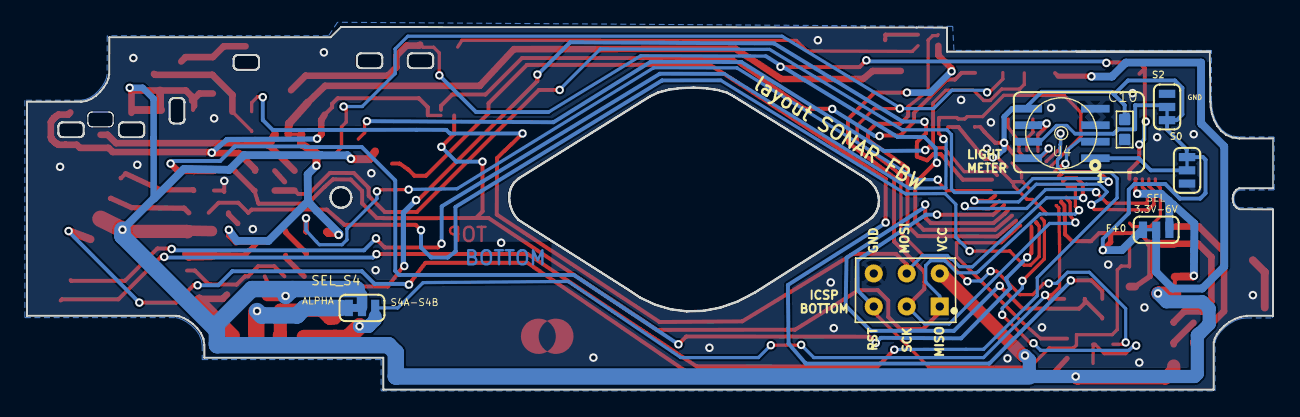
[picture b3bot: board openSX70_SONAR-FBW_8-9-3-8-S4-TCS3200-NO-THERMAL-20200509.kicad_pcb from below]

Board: 2 copper layers, 95.8 x 27.9 mm, 72 parts (6 on the bottom side), 52 nets.

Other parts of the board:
U$8: SONAR-LOGO

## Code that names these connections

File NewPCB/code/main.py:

from machine import Pin,PWM,ADC
import time

_CAMERA_DBG_ = True
Red_Button_Pressed = 1
if_focused = False
de_bounce_time = 1
de_bounce_count = 10
adc_de_bonuce_count = 70
# Code Start at "#End of Config"

# Config Output Pins <See Pins.xls>
shutter_pin = 9
apture_pin = 17
motor_pin = 5
LED_Y_PIN = 12
LED_B_PIN = 13
S1F_FBW_PIN = 22
# End Config Output

# Config Input Pins <See Pins.xls>
S1F_PIN = 2 # Sw 1 Focus
S1T_PIN = 1 # Sw 1 Take Photo
S3_PIN = 7
S5_PIN = 6
ADC_STAGE1_PIN = 27
ADC_STAGE2_PIN = 28
# End Config Input Pins

# Config ShutterDelay  sht(1/n) or sht(n)s
sht4s = 4000
sht3s = 3000
sht2s = 2000
sht1s = 1000
sht2 = 600
#ev75 = 440
sht4 = 280
sht6 =210
sht8 = 155
sht10 =120
sht15 = 97
sht20 = 70
sht30 = 48
#ev115 = 40
sht60 = 33
#ev125 = 29
sht125 = 25
#ev135 = 23
sht250 = 21
#ev145 = 20
sht500 = 19
sht1000 = 18
# End Config ShutterDelay

#End of Config

# Inital camera
def camera_init():
    global motor,shutter,apture,LED_Y,LED_B,s3,s5,s1t,s1f,S1F_FBW,ADC0,ADC1,iso
    shutter = PWM(Pin(shutter_pin))
    shutter.freq(20000)
    shutter.duty_u16(0)
    apture = PWM(Pin(apture_pin))
    apture.freq(70000)
    apture.duty_u16(0)
    
    motor = Pin(motor_pin,Pin.OUT, value=0)
    LED_Y = Pin(LED_Y_PIN, Pin.OUT,value = 1)
    LED_B = Pin(LED_B_PIN, Pin.OUT,value = 1)
    S1F_FBW = Pin(S1F_FBW_PIN, Pin.OUT,value = 0)
    
    s3 = Pin(S3_PIN,Pin.IN,Pin.PULL_UP)
    s5 = Pin(S5_PIN,Pin.IN,Pin.PULL_UP)
    s1f = Pin(S1F_PIN,Pin.IN)
    s1t = Pin(S1T_PIN,Pin.IN)
    
    ADC0 = ADC(Pin(ADC_STAGE1_PIN))  # 初始化ADC
    ADC1 = ADC(Pin(ADC_STAGE2_PIN))  # 初始化ADC
    
    f = open('./dat/iso.txt')
    iso = f.readline()
    iso.replace(" ","")
    f.close()
    if _CAMERA_DBG_:
        print("ISO at %s!"%iso)
    if iso == '600':
        LED_Y.value(0)
    else:
        LED_B.value(0)

def close_led():
    LED_Y.value(1)
    LED_B.value(1)
    
def led_iso():
    if iso == '600':
        LED_Y.value(0)
    else:
        LED_B.value(0)

def de_bounce_read_pins(pin_list):
    global de_bounce_time,de_bounce_count
    pin_value = [0]*len(pin_list)
    for i in range(de_bounce_count):
        for j in range(len(pin_list)):
            pin_value[j] += pin_list[j].value()
        time.sleep_ms(de_bounce_time)
    for i in range(len(pin_value)):
        pin_value[i] = round(pin_value[i]/de_bounce_count)
        if i >1:
            i = 1
    return pin_value

def apture_engage():
    apture.duty_u16(32700)
    
def apture_disengage():
    apture.duty_u16(0)

def meter():
    read_voltage0 = 0
    read_voltage1 = 0
    for i in range(adc_de_bonuce_count):
        read_voltage0 += ADC0.read_u16()*3000/65535   # 读取ADC通道0的数值并根据ADC电压计算公式得到GPIO26引脚上的电压
        read_voltage1 += ADC1.read_u16()*3000/65535   # 读取ADC通道0的数值并根据ADC电压计算公式得到GPIO26引脚上的电压
        time.sleep_ms(1)
    read_voltage0 = read_voltage0/adc_de_bonuce_count
    read_voltage1 = read_voltage1/adc_de_bonuce_count
    if _CAMERA_DBG_:
        print("1st stage voltage = {0:.2f}mV \t\t  2nd stage voltage = {1:.2f}mV \t\t".format(read_voltage0, read_voltage1))
    
        
    

def shut(Shutter_Delay, f="1"):
    if _CAMERA_DBG_:
        print("Taking Picture")
    if _CAMERA_DBG_:
        print("Shutter start to close!")
    shutter.duty_u16(65535)
    time.sleep_ms(18)
    shutter.duty_u16(10000)
    motor.value(1)
    if _CAMERA_DBG_:
        print("Motor Start Moving")
    while True:
        if s3.value() == 1:
            motor.value(0)
            if _CAMERA_DBG_:
                print("Motor Stoped!")
            break
        
    if f=='0': #Engage apture
        apture_engage() 
    time.sleep_ms(18) # Y delay
    
    shutter.duty_u16(0) #open shutter
    if _CAMERA_DBG_:
        print("Shutter Start to Open, Exposure Starts")

    # Start Exposure
    if f == '0':
        if _CAMERA_DBG_:
            print("Flash Mode!")
        gap=int(Shutter_Delay*0.3)
        time.sleep_ms(gap)
        fl.value(1)
        time.sleep_ms(gap)
        fl.value(0)
        apture_disengage() # Apture goes back
        time.sleep_ms(gap)
    elif f == '1':
        time.sleep_ms(Shutter_Delay)
    elif f == 'B':
        time.sleep_ms(15)
        while True:
            time.sleep_ms(3)
            if btn.value() == 1:
                break
    elif f == 'T':
        time.sleep(100)
        while True:
            time.sleep(3)
            if btn.value() == 0:
                break
    # End Exposure
    
    shutter.duty_u16(65535) # Close Shutter
    if _CAMERA_DBG_:
        print("Shutter Closing!")
    time.sleep_ms(20)
    shutter.duty_u16(10000) # Keep Shutter Closed
    if _CAMERA_DBG_:
        print("Shutter Closd. Exposure Finished")
    
    motor.value(1)
    if _CAMERA_DBG_:
        print("Motor Working!")
    while True:
        if s5.value() == 0:
            motor.value(0)
            shutter.duty_u16(0)
            break
        

def test_cam():
    time.sleep_ms(3800)
    LED_Y.value(1)
    shutter.duty_u16(65535)
    time.sleep_ms(3800)
    shutter.duty_u16(0)
    motor.value(1)
    LED_Y.value(0)
    
def test_cam1():
    global if_focused, CAMERA_DBG
    while True:
        dbpv = de_bounce_read_pins([s1f,s1t])
        foc = dbpv[0]
        tak = dbpv[1]
        if foc == Red_Button_Pressed and if_focused == False:
            #S1F_FBW.value(1);
            if_focused = True
            print("Focusing!")
            if _CAMERA_DBG_:
                print(dbpv)
        if foc != Red_Button_Pressed and if_focused == True:
            #S1F_FBW.value(0);
            if_focused = False
            print("Stop Focus")
            if _CAMERA_DBG_:
                print(dbpv)
        if tak == Red_Button_Pressed:
            meter()
            LED_Y.value(1)
            LED_B.value(1)
            shut(1000);
            print("Taken!")
            led_iso()
            
            if _CAMERA_DBG_:
                print(dbpv)
            #return
    
if __name__ == "__main__":
    camera_init()
    #test_cam()
    #shut(1000)
    test_cam1()
    while True:
        meter()
        time.sleep_ms(1000)

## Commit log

2023-04-16 work
2023-04-18 PCB finished
    finished pcb designing, god bless it would work.
2023-04-19 test appliance
2023-04-20 Test Pin Holder for Bare Pcb
2023-04-20 Del opt
2023-04-24 code
2023-04-24 iso display
2023-04-24 adc_finished
2023-04-24 Meter not finish
2023-04-24 body_tested
2023-04-24 del some backup
2023-04-25 meter cal.
2023-04-25 speed adjusted
2023-05-05 good
2023-05-05 Rev2 Finished
2023-05-06 added screen
2023-05-07 cliper
2023-05-10 Body Controller
2023-05-10 flash_tested & PCB Rev 2.1
2023-05-11 Organize files
2023-05-11 controller finished
2023-05-15 controller manufacture & todo list
2023-05-16 repaired cliper
2023-05-19 cliper_update
2023-05-20 cliper updated && fill in flash code finished
2023-05-22 case
2023-05-22 code upgrade
2023-05-23 case refined
2023-05-27 Body Controller 3D models
2023-05-28 Body Controller Basic Function
2023-05-30 Assembled and tested
